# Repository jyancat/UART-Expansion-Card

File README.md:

# UART Expansion Card
Design files for the UART expansion card, please note this is a tested and working expansion card. Licensed under CERN-OHL-S-2.0. Uses the CH340C with switchable power and logic levels (5V and 3V3) Please note that the files in the 3D Printer Files directory are not finalised. Part numbers in the BOM may be diffent to what you do recieve due to supply and cost changes.

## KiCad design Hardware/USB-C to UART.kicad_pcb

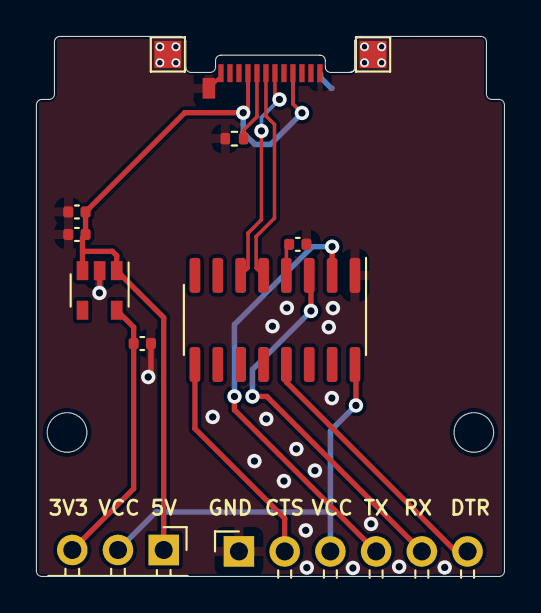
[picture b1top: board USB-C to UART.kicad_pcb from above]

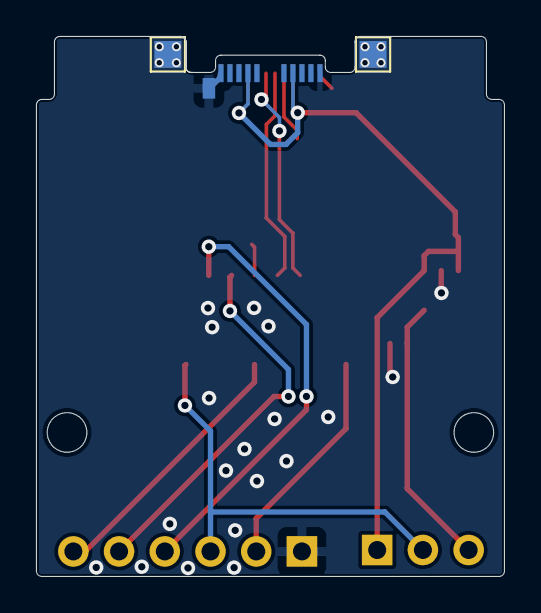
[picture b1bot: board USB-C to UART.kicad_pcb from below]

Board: 2 copper layers, 26.0 x 30.0 mm, 16 parts (2 on the bottom side), 12 nets.

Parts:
C1: 0.1uF; C_0402_1005Metric
C2: 10nF; C_0402_1005Metric
C3, C4: 1uF; C_0402_1005Metric
H1, H2: MountingHole; MountingHole_2.2mm_M2
J1: Conn_01x06_Female; PinSocket_1x06_P2.54mm_Horizontal
JP1: Jumper_3_Open; PinHeader_1x03_P2.54mm_Horizontal
P1: 105444-0001; USB_C_Plug_Molex_105444
R1: 5.1k; R_0402_1005Metric
TP1, TP2, TP3, TP4: TestPoint; TestPoint_Pad_1.5x1.5mm
U1: CH340C; SOIC-16_3.9x9.9mm_P1.27mm
U2: AP2112K-3.3; SOT-23-5

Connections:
3V3: C4.1, JP1.3, U2.5
5V: C1.1, C3.1, JP1.1, P1.A4, P1.A9, P1.B4, P1.B9, U2.1, U2.3
CTS: J1.2, U1.9
D+: P1.A6, U1.5
D-: P1.A7, U1.6
DTR: J1.6, U1.13
Earth: C1.2, C2.2, C3.2, C4.2, J1.1, P1.A1, P1.A12, P1.B1, P1.B12, P1.S1, R1.1, TP1.1, TP2.1, TP3.1, TP4.1, U1.1, U2.2
unnamed: C2.1, U1.4
unnamed: P1.A5, R1.2
RXI: J1.5, U1.3
TXO: J1.4, U1.2
VCC: J1.3, JP1.2, U1.16

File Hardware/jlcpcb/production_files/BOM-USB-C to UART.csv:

Comment,Designator,Footprint,LCSC
5.1k,R1,R_0402_1005Metric,C105872
10nF,C2,C_0402_1005Metric,C15195
0.1uF,C1,C_0402_1005Metric,C1525
Conn_01x06_Female,J1,PinSocket_1x06_P2.54mm_Horizontal,C3323404
Jumper_3_Open,JP1,PinHeader_1x03_P2.54mm_Horizontal,C3347958
AP2112K-3.3,U2,SOT-23-5,C427602
1uF,"C3,C4",C_0402_1005Metric,C52923
105444-0001,P1,USB_C_Plug_Molex_105444,C561769
CH340C,U1,SOIC-16_3.9x9.9mm_P1.27mm,C84681

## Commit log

2022-05-04 Add.
2022-05-04 Updated Schematic
2022-05-27 Updated Files
2022-08-07 Added new files
2022-08-07 Create LICENSE
2022-08-08 Update LICENSE
2022-08-08 Create LICENCE
2022-08-18 Added new files, documentation and OSHWA
2022-08-18 Added other files
2024-08-14 Updated to latest design files
